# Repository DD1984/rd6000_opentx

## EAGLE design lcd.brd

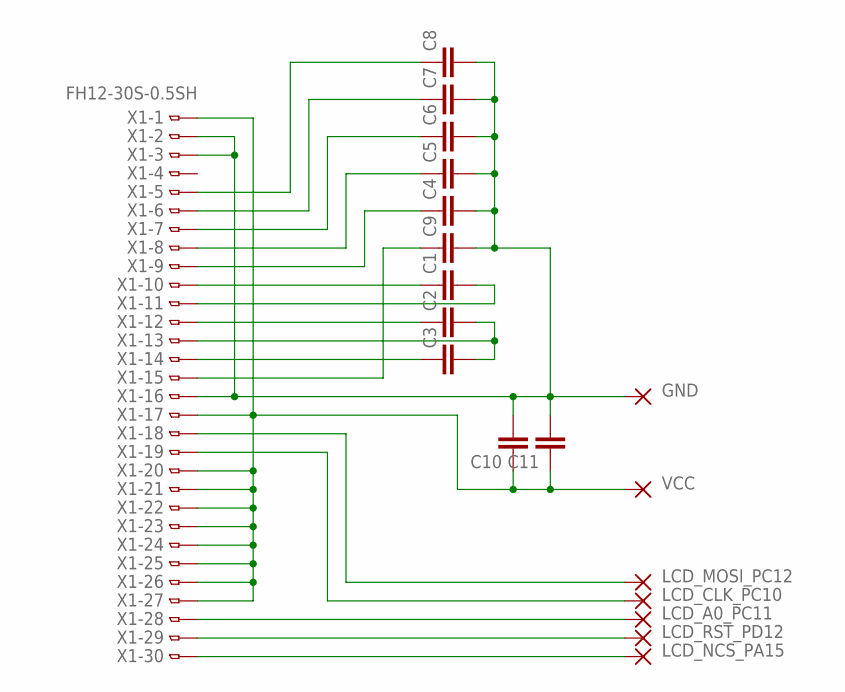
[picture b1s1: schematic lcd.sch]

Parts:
C1, C2, C3, C4, C5, C6, C7, C8, C9, C10, C11: C-EUC0805; C0805
PAD1, PAD2, PAD3, PAD4, PAD5, PAD6, PAD7: WIREPADSMD5-2,5; 5-2,5
X1: FH12-30S-0.5SH

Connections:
GND: C4.2, C5.2, C6.2, C7.2, C8.2, C9.2, C10.2, C11.2, PAD6.1, X1.2, X1.3, X1.16
LCD_A0_PC11: PAD3.1, X1.28
LCD_CLK_PC10: PAD2.1, X1.19
LCD_MOSI_PC12: PAD1.1, X1.18
LCD_NCS_PA15: PAD5.1, X1.30
LCD_RST_PD12: PAD4.1, X1.29
unnamed: C1.1, X1.10
unnamed: C9.1, X1.15
unnamed: C4.1, X1.9
unnamed: C5.1, X1.8
unnamed: C6.1, X1.7
unnamed: C7.1, X1.6
unnamed: C8.1, X1.5
unnamed: C3.1, X1.14
unnamed: C2.2, C3.2, X1.13
unnamed: C2.1, X1.12
unnamed: C1.2, X1.11
VCC: C10.1, C11.1, PAD7.1, X1.1, X1.17, X1.20, X1.21, X1.22, X1.23, X1.24, X1.25, X1.26, X1.27

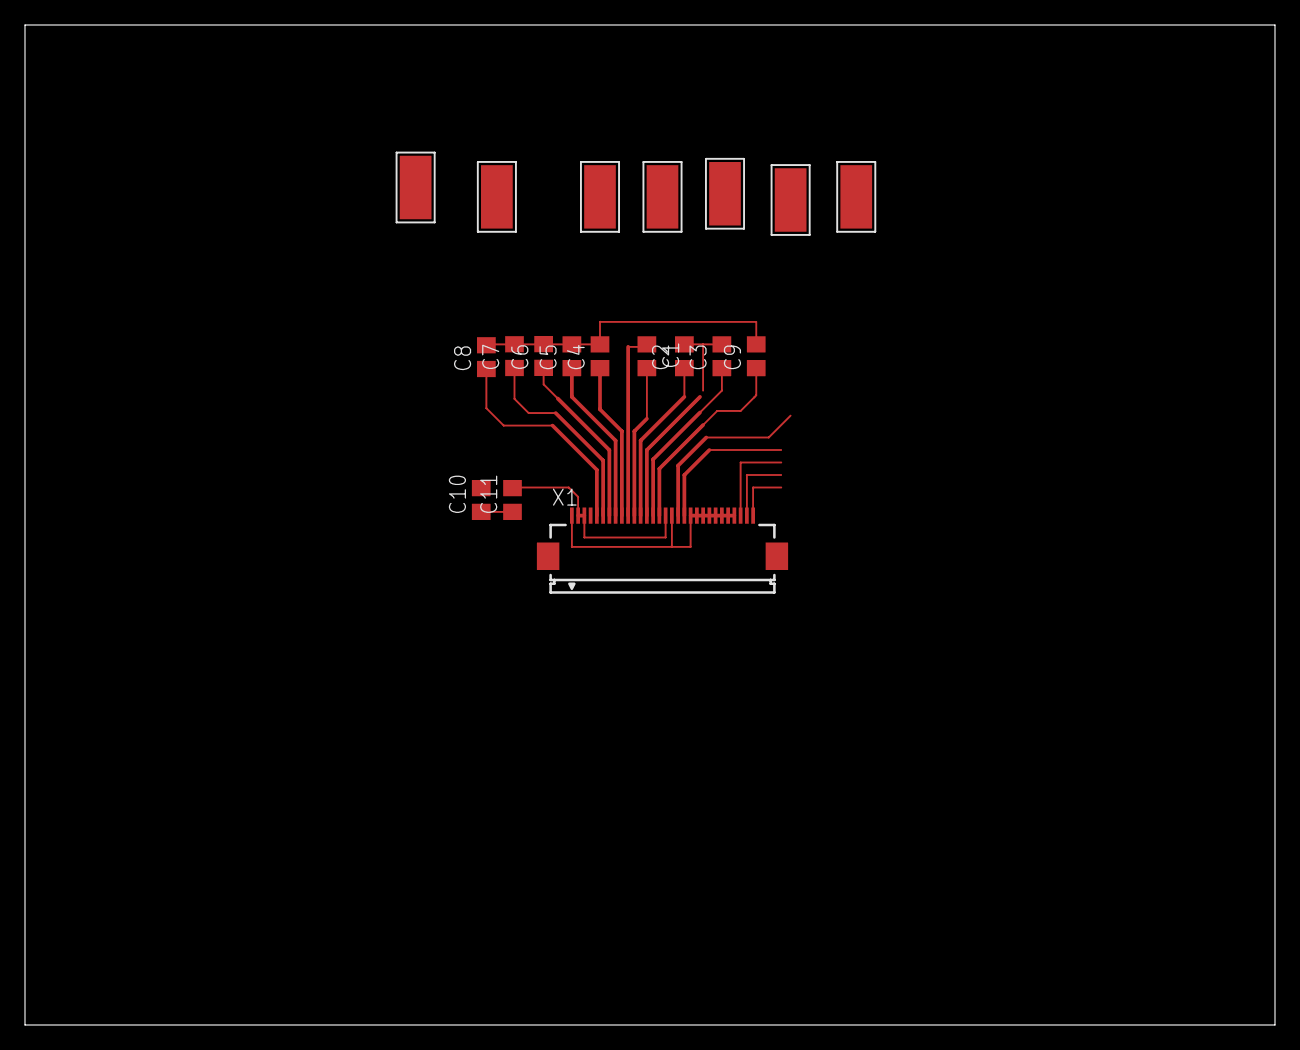
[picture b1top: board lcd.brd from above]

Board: 2 copper layers, 100.0 x 80.0 mm, 19 parts (0 on the bottom side), 18 nets.

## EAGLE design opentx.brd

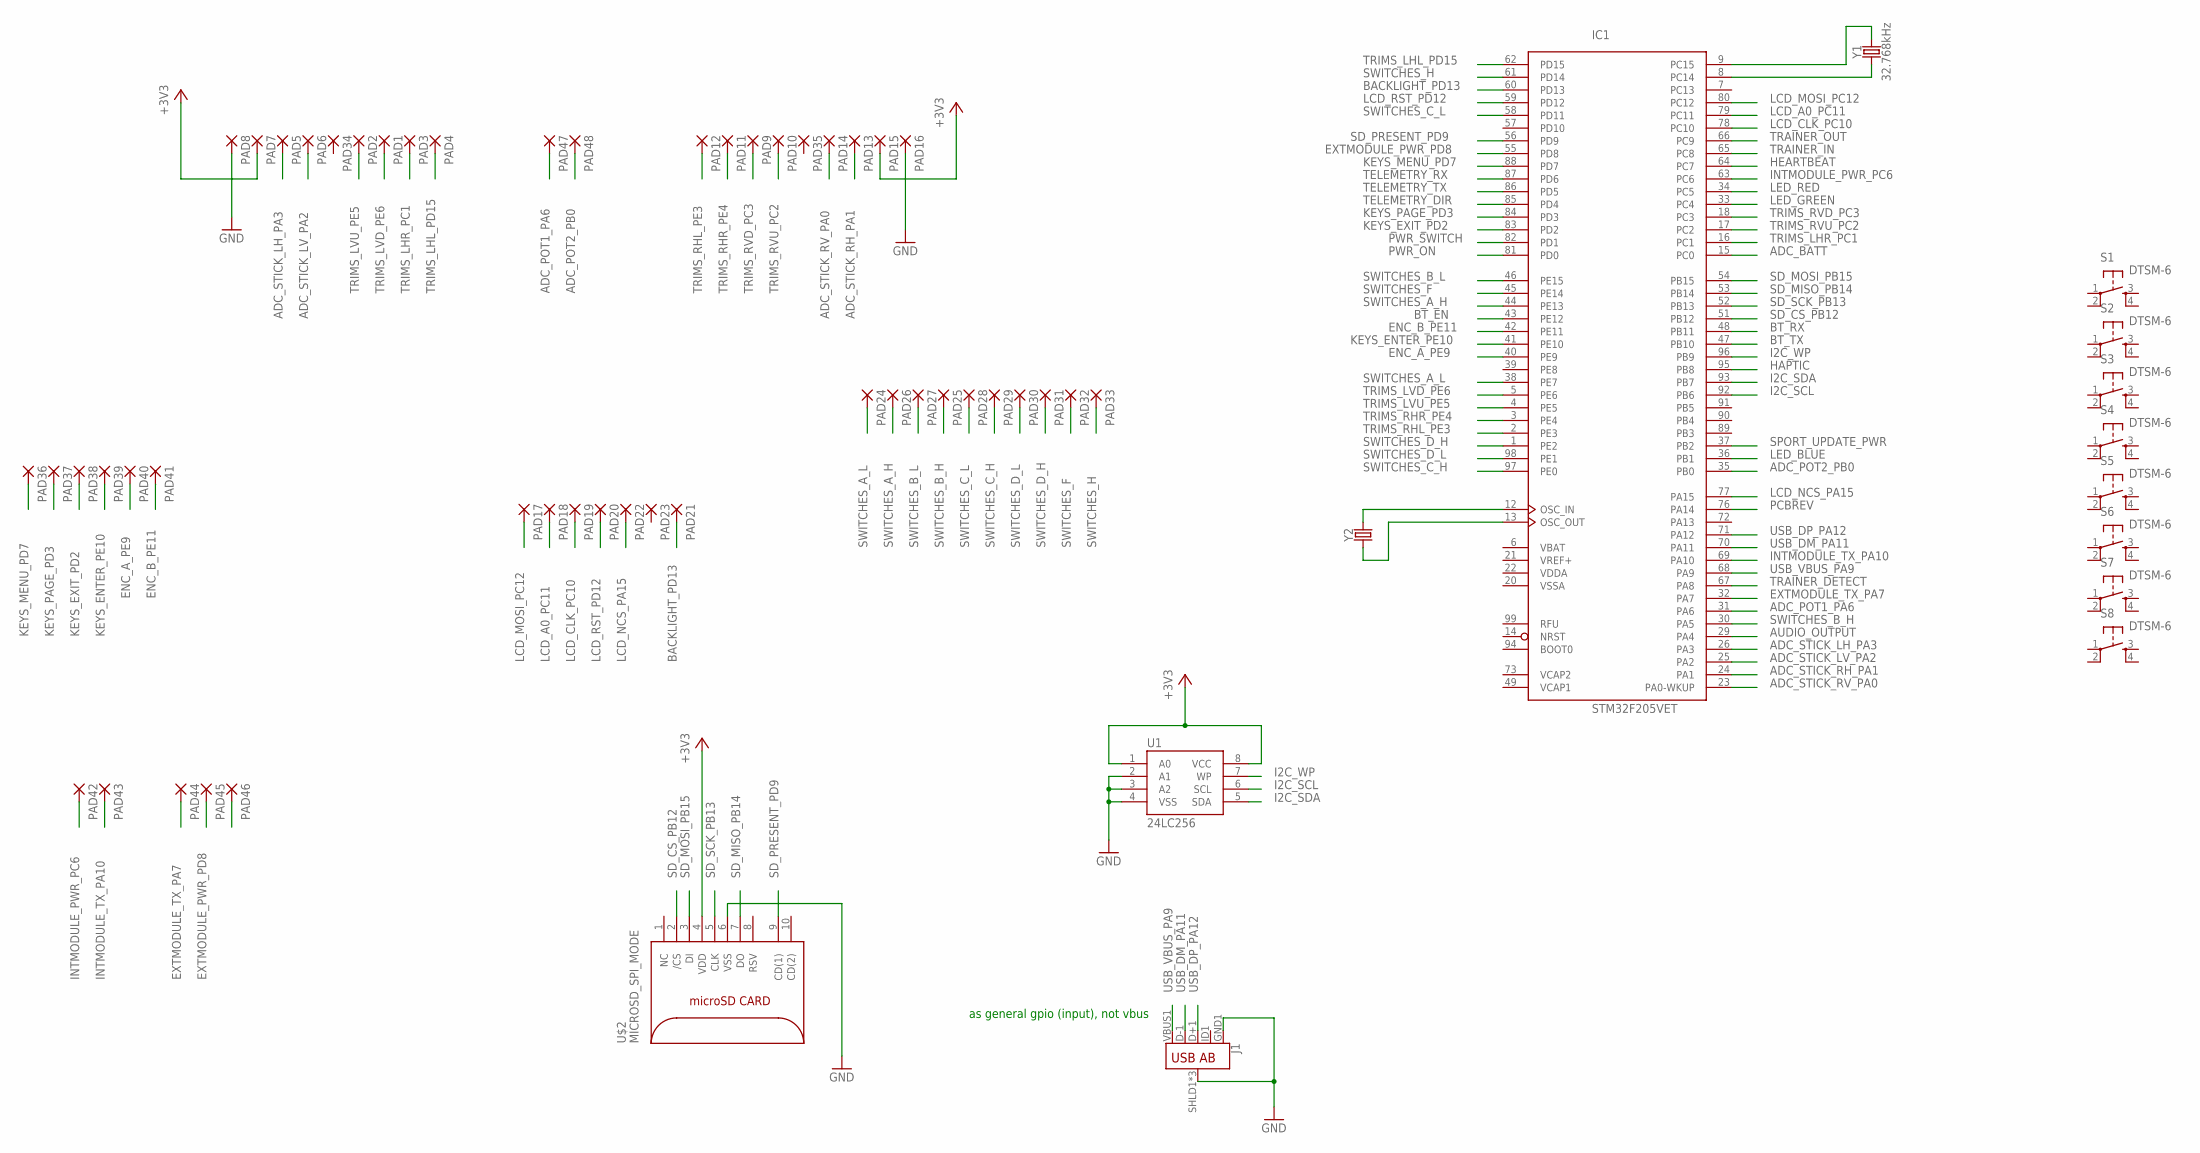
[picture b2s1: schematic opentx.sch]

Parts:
IC1: STM32F205VET; LQFP100
J1: USB_AB_SMT; USB-AB-MICRO-SMD
PAD1, PAD2, PAD3, PAD4, PAD5, PAD6, PAD7, PAD8, PAD9, PAD10, PAD11, PAD12, PAD13, PAD14, PAD15, PAD16, PAD17, PAD18, PAD19, PAD20, PAD21, PAD22, PAD23, PAD24, PAD25, PAD26, PAD27, PAD28, PAD29, PAD30, PAD31, PAD32, PAD33, PAD34, PAD35, PAD36, PAD37, PAD38, PAD39, PAD40, PAD41, PAD42, PAD43, PAD44, PAD45, PAD46, PAD47, PAD48: SMD2; SMD1,27-2,54
S1, S2, S3, S4, S5, S6, S7, S8: DTSM-6
U1: 24LC256; SO08
U$2: MICROSD_SPI_MODE; MICRO_SD_CONNECTOR
Y1: 32.768kHz; CRYSTAL-SMD-2X6-CYL
Y2: CRYSTALSMD-HC49UP; HC49UP

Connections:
+3V3: PAD7.1, PAD15.1, U1.1 (A0), U1.8 (VCC), U$2.4 (VDD)
ADC_BATT: IC1.15 (PC0)
ADC_POT1_PA6: IC1.31 (PA6), PAD47.1
ADC_POT2_PB0: IC1.35 (PB0), PAD48.1
ADC_STICK_LH_PA3: IC1.26 (PA3), PAD5.1
ADC_STICK_LV_PA2: IC1.25 (PA2), PAD6.1
ADC_STICK_RH_PA1: IC1.24 (PA1), PAD13.1
ADC_STICK_RV_PA0: IC1.23 (PA0-WKUP), PAD14.1
AUDIO_OUTPUT: IC1.29 (PA4)
BACKLIGHT_PD13: IC1.60 (PD13), PAD21.1
BT_EN: IC1.43 (PE12)
BT_RX: IC1.48 (PB11)
BT_TX: IC1.47 (PB10)
ENC_A_PE9: IC1.40 (PE9), PAD40.1
ENC_B_PE11: IC1.42 (PE11), PAD41.1
EXTMODULE_PWR_PD8: IC1.55 (PD8), PAD45.1
EXTMODULE_TX_PA7: IC1.32 (PA7), PAD44.1
GND: J1.GND1 (GND), J1.SHLD1 (SHIELD), J1.SHLD2 (SHIELD), J1.SHLD3 (SHIELD), PAD8.1, PAD16.1, U1.2 (A1), U1.3 (A2), U1.4 (VSS), U$2.6 (VSS)
HAPTIC: IC1.95 (PB8)
HEARTBEAT: IC1.64 (PC7)
I2C_SCL: IC1.92 (PB6), U1.6 (SCL)
I2C_SDA: IC1.93 (PB7), U1.5 (SDA)
I2C_WP: IC1.96 (PB9), U1.7 (WP)
INTMODULE_PWR_PC6: IC1.63 (PC6), PAD42.1
INTMODULE_TX_PA10: IC1.69 (PA10), PAD43.1
KEYS_ENTER_PE10: IC1.41 (PE10), PAD39.1
KEYS_EXIT_PD2: IC1.83 (PD2), PAD38.1
KEYS_MENU_PD7: IC1.88 (PD7), PAD36.1
KEYS_PAGE_PD3: IC1.84 (PD3), PAD37.1
LCD_A0_PC11: IC1.79 (PC11), PAD18.1
LCD_CLK_PC10: IC1.78 (PC10), PAD19.1
LCD_MOSI_PC12: IC1.80 (PC12), PAD17.1
LCD_NCS_PA15: IC1.77 (PA15), PAD22.1
LCD_RST_PD12: IC1.59 (PD12), PAD20.1
LED_BLUE: IC1.36 (PB1)
LED_GREEN: IC1.33 (PC4)
LED_RED: IC1.34 (PC5)
unnamed: IC1.8 (PC14), Y1.X1 (1)
unnamed: IC1.9 (PC15), Y1.X2 (2)
unnamed: IC1.12 (OSC_IN), Y2.2
unnamed: IC1.13 (OSC_OUT), Y2.1
PCBREV: IC1.76 (PA14)
PWR_ON: IC1.81 (PD0)
PWR_SWITCH: IC1.82 (PD1)
SD_CS_PB12: IC1.51 (PB12), U$2.2 (/CS)
SD_MISO_PB14: IC1.53 (PB14), U$2.7 (DO)
SD_MOSI_PB15: IC1.54 (PB15), U$2.3 (DI)
SD_PRESENT_PD9: IC1.56 (PD9), U$2.9 (CD(1))
SD_SCK_PB13: IC1.52 (PB13), U$2.5 (CLK)
SPORT_UPDATE_PWR: IC1.37 (PB2)
SWITCHES_A_H: IC1.44 (PE13), PAD26.1
SWITCHES_A_L: IC1.38 (PE7), PAD24.1
SWITCHES_B_H: IC1.30 (PA5), PAD25.1
SWITCHES_B_L: IC1.46 (PE15), PAD27.1
SWITCHES_C_H: IC1.97 (PE0), PAD29.1
SWITCHES_C_L: IC1.58 (PD11), PAD28.1
SWITCHES_D_H: IC1.1 (PE2), PAD31.1
SWITCHES_D_L: IC1.98 (PE1), PAD30.1
SWITCHES_F: IC1.45 (PE14), PAD32.1
SWITCHES_H: IC1.61 (PD14), PAD33.1
TELEMETRY_DIR: IC1.85 (PD4)
TELEMETRY_RX: IC1.87 (PD6)
TELEMETRY_TX: IC1.86 (PD5)
TRAINER_DETECT: IC1.67 (PA8)
TRAINER_IN: IC1.65 (PC8)
TRAINER_OUT: IC1.66 (PC9)
TRIMS_LHL_PD15: IC1.62 (PD15), PAD4.1
TRIMS_LHR_PC1: IC1.16 (PC1), PAD3.1
TRIMS_LVD_PE6: IC1.5 (PE6), PAD1.1
TRIMS_LVU_PE5: IC1.4 (PE5), PAD2.1
TRIMS_RHL_PE3: IC1.2 (PE3), PAD12.1
TRIMS_RHR_PE4: IC1.3 (PE4), PAD11.1
TRIMS_RVD_PC3: IC1.18 (PC3), PAD9.1
TRIMS_RVU_PC2: IC1.17 (PC2), PAD10.1
USB_DM_PA11: IC1.70 (PA11), J1.D-1 (D-)
USB_DP_PA12: IC1.71 (PA12), J1.D+1 (D+)
USB_VBUS_PA9: IC1.68 (PA9), J1.VBUS1 (VBUS)
VBAT: IC1.6 (VBAT)
VCAP1: IC1.49 (VCAP1)
VCAP2: IC1.73 (VCAP2)
VDD: IC1.11 (VDD), IC1.19 (VDD), IC1.28 (VDD), IC1.50 (VDD), IC1.75 (VDD), IC1.100 (VDD)
VDDA: IC1.22 (VDDA)
VREF+: IC1.21 (VREF+)
VSS: IC1.10 (VSS), IC1.27 (VSS), IC1.74 (VSS)
VSSA: IC1.20 (VSSA)

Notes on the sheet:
as general gpio (input), not vbus

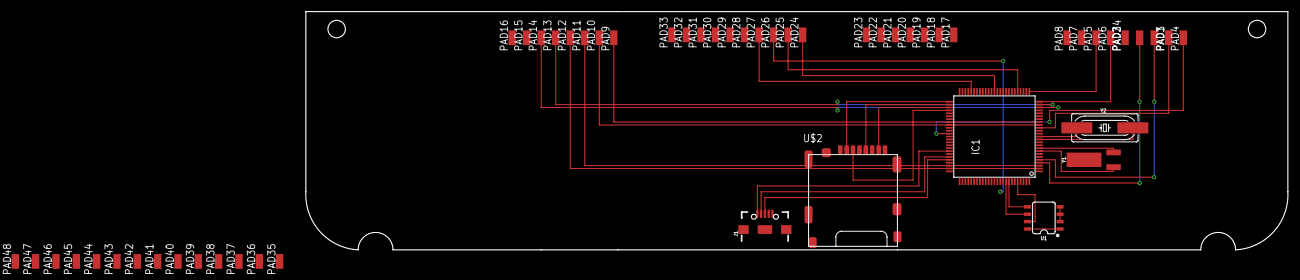
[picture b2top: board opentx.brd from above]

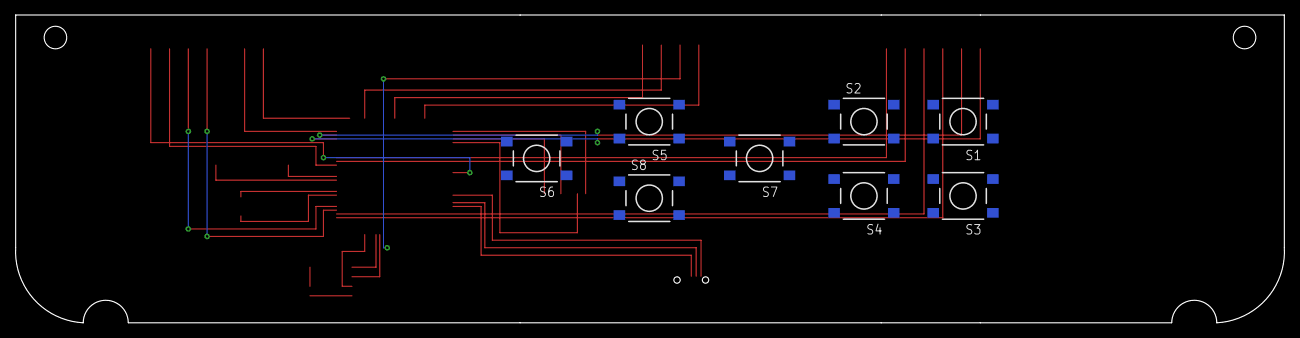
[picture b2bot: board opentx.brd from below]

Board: 2 copper layers, 169.0 x 40.9 mm, 62 parts (8 on the bottom side), 59 nets.

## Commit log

2018-12-21 start pcb
2018-12-28 original pcb photos
2019-04-04 scheme
2019-04-05 gitignore
2019-04-07 scheme & photo

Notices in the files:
parts and their libraries:
SparkFun-IC-Memory: Licensing: Creative Commons ShareAlike 4.0 International - https://creativecommons.org/licenses/by-sa/4.0
